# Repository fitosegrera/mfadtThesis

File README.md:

# mfadtThesis

####Setup UDOO Board

Install the VNC server:

1.Open a terminal window and type:

	sudo apt-get update

	sudo apt-get install tightvncserver

2. Run the server:

	vncserver :1 -geometry 800x600 -depth 24

3. Make the server run on every boot:

	sudo nano /etc/rc.local

The document will open on your terminal window, using your keyboard keys go to the line just before "exit0" and type:

	vncserver :1 -geometry 800x600 -depth 24 &

4. Before any further step, we will configure the udoo to have a STATIC IP Address. This in order to ensure the wireless connection to the local network. For the local network I'm using a linksis wireless router with a hidden network. To configure the udoo IP do the following:

	4.1 Go to Menu>Preferences>Network Connections

	4.2 Select the Wireless tab
	
	4.3 with your network name highlighted, click on EDIT

	4.4 go to the IPV4 tab and change from automatic to manual

	4.5 Finally Add a new IP Address(What ever address you want to assign to the udoo), a NETMASK (usually 255.255.255.0) and your GATEWAY(router's IP)

	4.6 Save your changes...

To remotly control your UDOO board you will need to install a VNC client. For windows and Mac I recomend REALVNC.
For linux xvncviewer. To install in linux go to your terminal and type:

	sudo apt-get install xvnc4viewer

To use the client from a linux computer type:

	sudo xvncviewer

Then just type your UDOO's ip followed by the port (replace udoo.ip.address with your udoo's ip address, the port remains the same):

	udoo.ip.address:5901

####Run a python script using foreverjs

	forever start -c python python_script.py

Stopping forever

	forever stopall

####htop process monitoring

	sudo apt-get install htop

to run the application type:

	htop

To filter processes to match only python scripts. Press the f4 key and in the text bar type: .py 

####PyPy

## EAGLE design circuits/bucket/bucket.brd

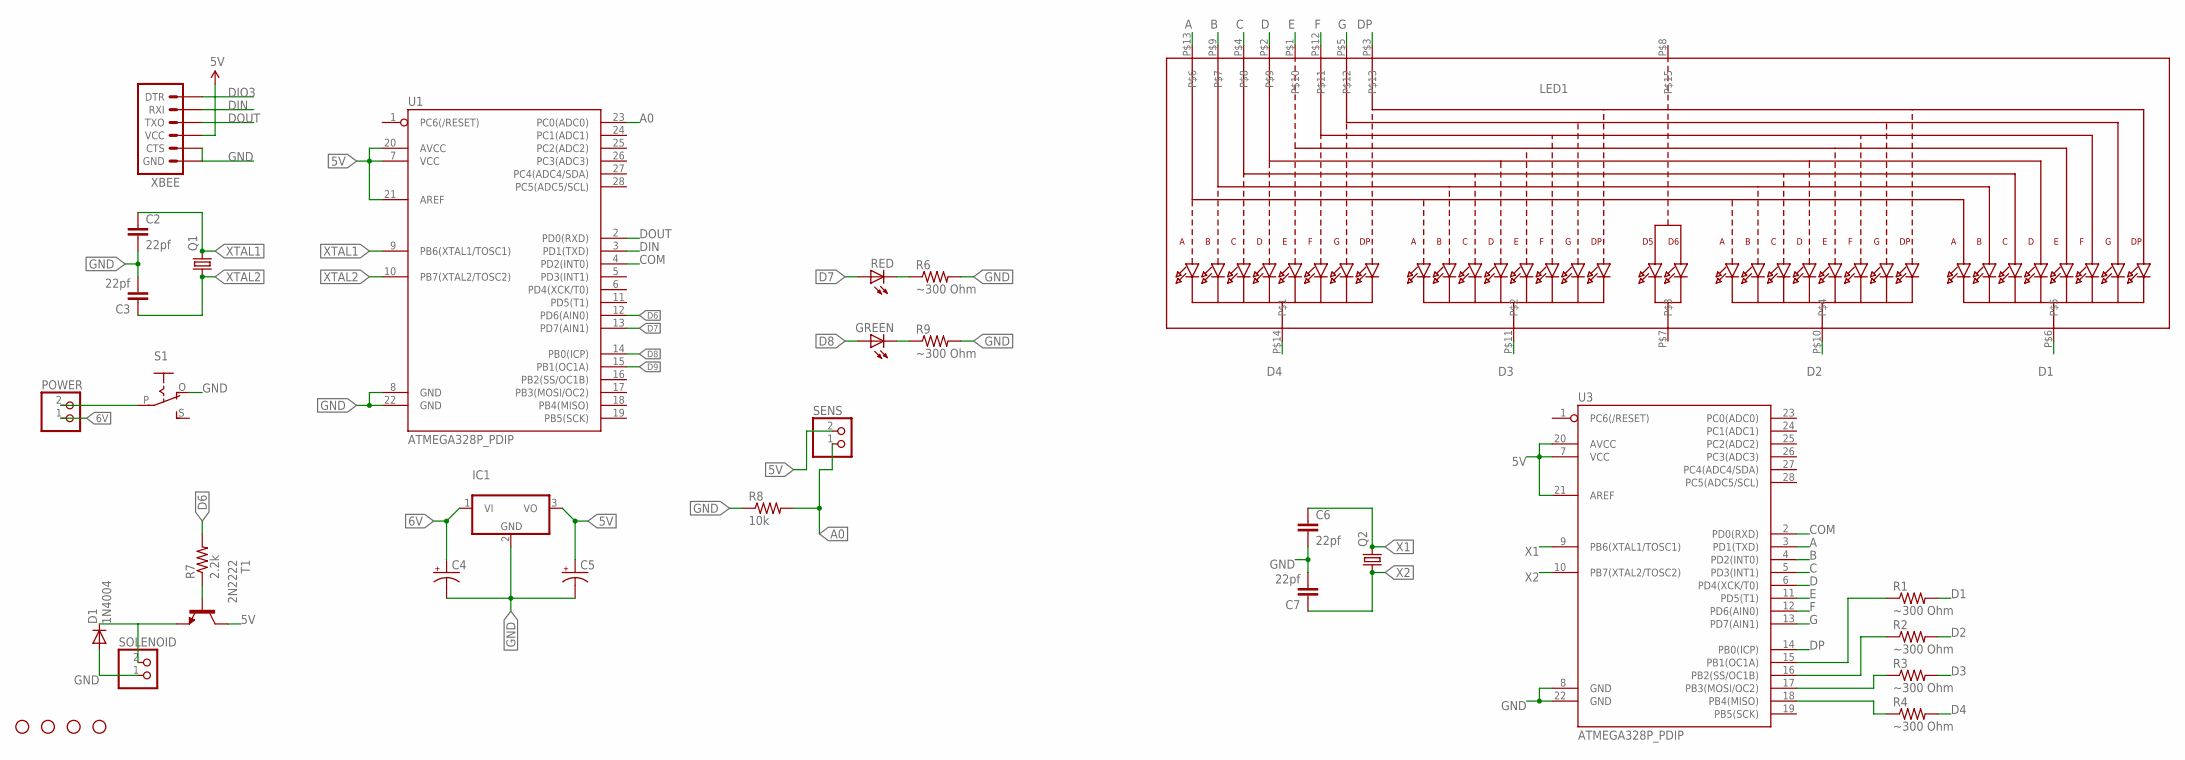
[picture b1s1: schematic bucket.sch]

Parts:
C2, C3, C6, C7: 22pf; 1206
C4, C5: CAP_POL1206; EIA3216
D1: 1N4004; DO41-10
GREEN: HSMC-C265
IC1: 7805T; TO220H
LED1: DISP_SEGMENT_4DIGIT_BL-Q56C43; SEGMENT-BL-Q56C43
POWER: JST_2PIN-THM-RA; JST-PH-2-THM-RA
Q1, Q2: CRYSTALHC49S; HC49/S
R1, R2, R3, R4, R6, R9: ~300 Ohm; 1206
R7: 2.2k; 1206
R8: 10k; 1206
RED: HSMC-C265
S1: EG1218S; EG1218
SENS: JST_2PIN-THM-RA; JST-PH-2-THM-RA
SOLENOID: JST_2PIN-THM-RA; JST-PH-2-THM-RA
STANDOFF1, STANDOFF2, STANDOFF3, STANDOFF4: STAND-OFF
T1: 2N2222; TO92-EBC-OVAL
U1, U3: ATMEGA328P_PDIP; DIL28-3
XBEE: ARDUINO_SERIAL_PROGRAMPTH; 1X06

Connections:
1: R1.1, U3.15 (PB1(OC1A))
2: R2.1, U3.16 (PB2(SS/OC1B))
3: R3.1, U3.17 (PB3(MOSI/OC2))
4: R4.1, U3.18 (PB4(MISO))
5V: C5.A (+), IC1.3 (VO), SENS.2 (1), T1.E (C), U1.7 (VCC), U1.20 (AVCC), U1.21 (AREF), U3.7 (VCC), U3.20 (AVCC), U3.21 (AREF), XBEE.4 (VCC)
6V: C4.A (+), IC1.1 (VI), POWER.1 (2)
A: LED1.P$13, U3.3 (PD1(TXD))
A0: R8.2, SENS.1 (2), U1.23 (PC0(ADC0))
B: LED1.P$9, U3.4 (PD2(INT0))
C: LED1.P$4, U3.5 (PD3(INT1))
COM: U1.4 (PD2(INT0)), U3.2 (PD0(RXD))
D: LED1.P$2, U3.6 (PD4(XCK/T0))
D1: LED1.P$6, R1.2
D2: LED1.P$10, R2.2
D3: LED1.P$11, R3.2
D4: LED1.P$14, R4.2
D6: R7.2, U1.12 (PD6(AIN0))
D7: RED.A, U1.13 (PD7(AIN1))
D8: GREEN.A, U1.14 (PB0(ICP))
D9: U1.15 (PB1(OC1A))
DIN: U1.3 (PD1(TXD)), XBEE.2 (RXI)
DIO3: XBEE.1 (DTR)
DOUT: U1.2 (PD0(RXD)), XBEE.3 (TXO)
DP: LED1.P$3, U3.14 (PB0(ICP))
E: LED1.P$1, U3.11 (PD5(T1))
F: LED1.P$12, U3.12 (PD6(AIN0))
G: LED1.P$5, U3.13 (PD7(AIN1))
GND: C2.2, C3.2, C4.C (-), C5.C (-), C6.2, C7.2, D1.A, IC1.2 (GND), R6.2, R8.1, R9.2, S1.O, SOLENOID.1 (2), U1.8 (GND), U1.22 (GND), U3.8 (GND), U3.22 (GND), XBEE.5 (CTS), XBEE.6 (GND)
unnamed: POWER.2 (1), S1.P
unnamed: D1.C, SOLENOID.2 (1), T1.C (E)
unnamed: R6.1, RED.C
unnamed: R7.1, T1.B
unnamed: GREEN.C, R9.1
X1: C6.1, Q2.2, U3.9 (PB6(XTAL1/TOSC1))
X2: C7.1, Q2.1, U3.10 (PB7(XTAL2/TOSC2))
XTAL1: C2.1, Q1.2, U1.9 (PB6(XTAL1/TOSC1))
XTAL2: C3.1, Q1.1, U1.10 (PB7(XTAL2/TOSC2))

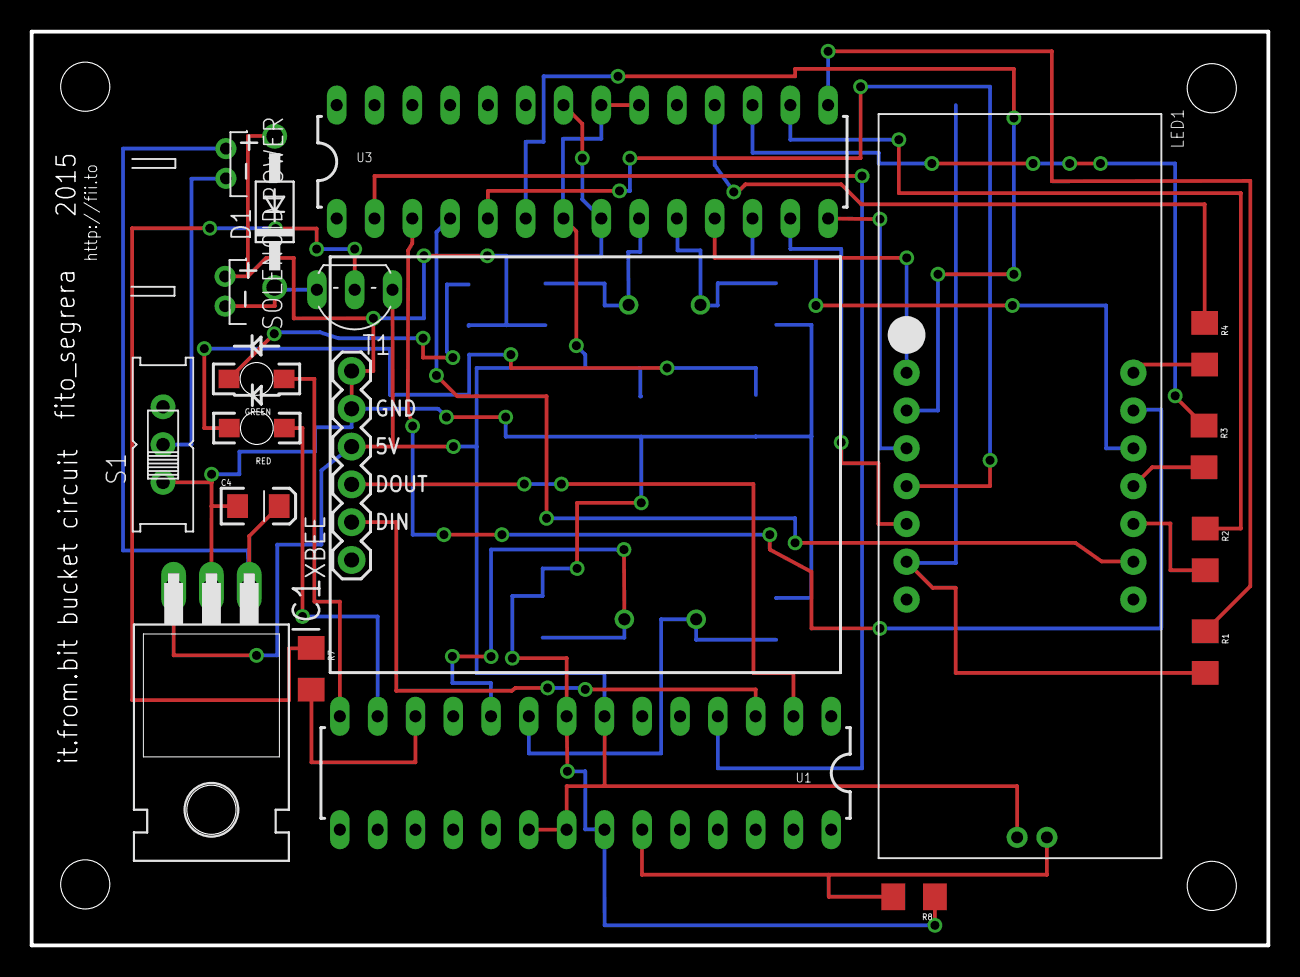
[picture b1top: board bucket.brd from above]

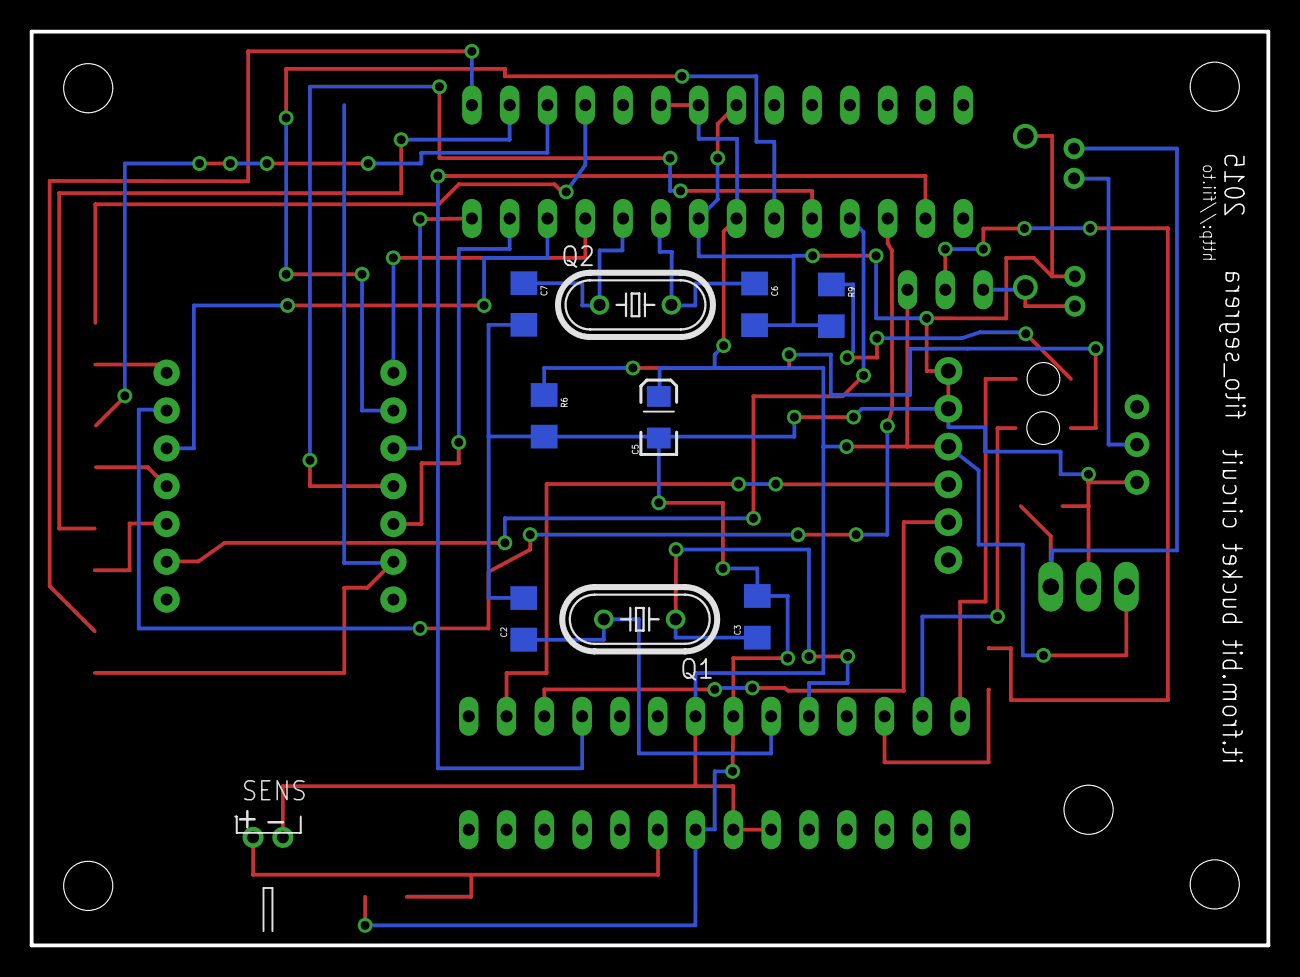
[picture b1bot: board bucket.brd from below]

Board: 2 copper layers, 83.1 x 61.4 mm, 33 parts (10 on the bottom side), 35 nets.

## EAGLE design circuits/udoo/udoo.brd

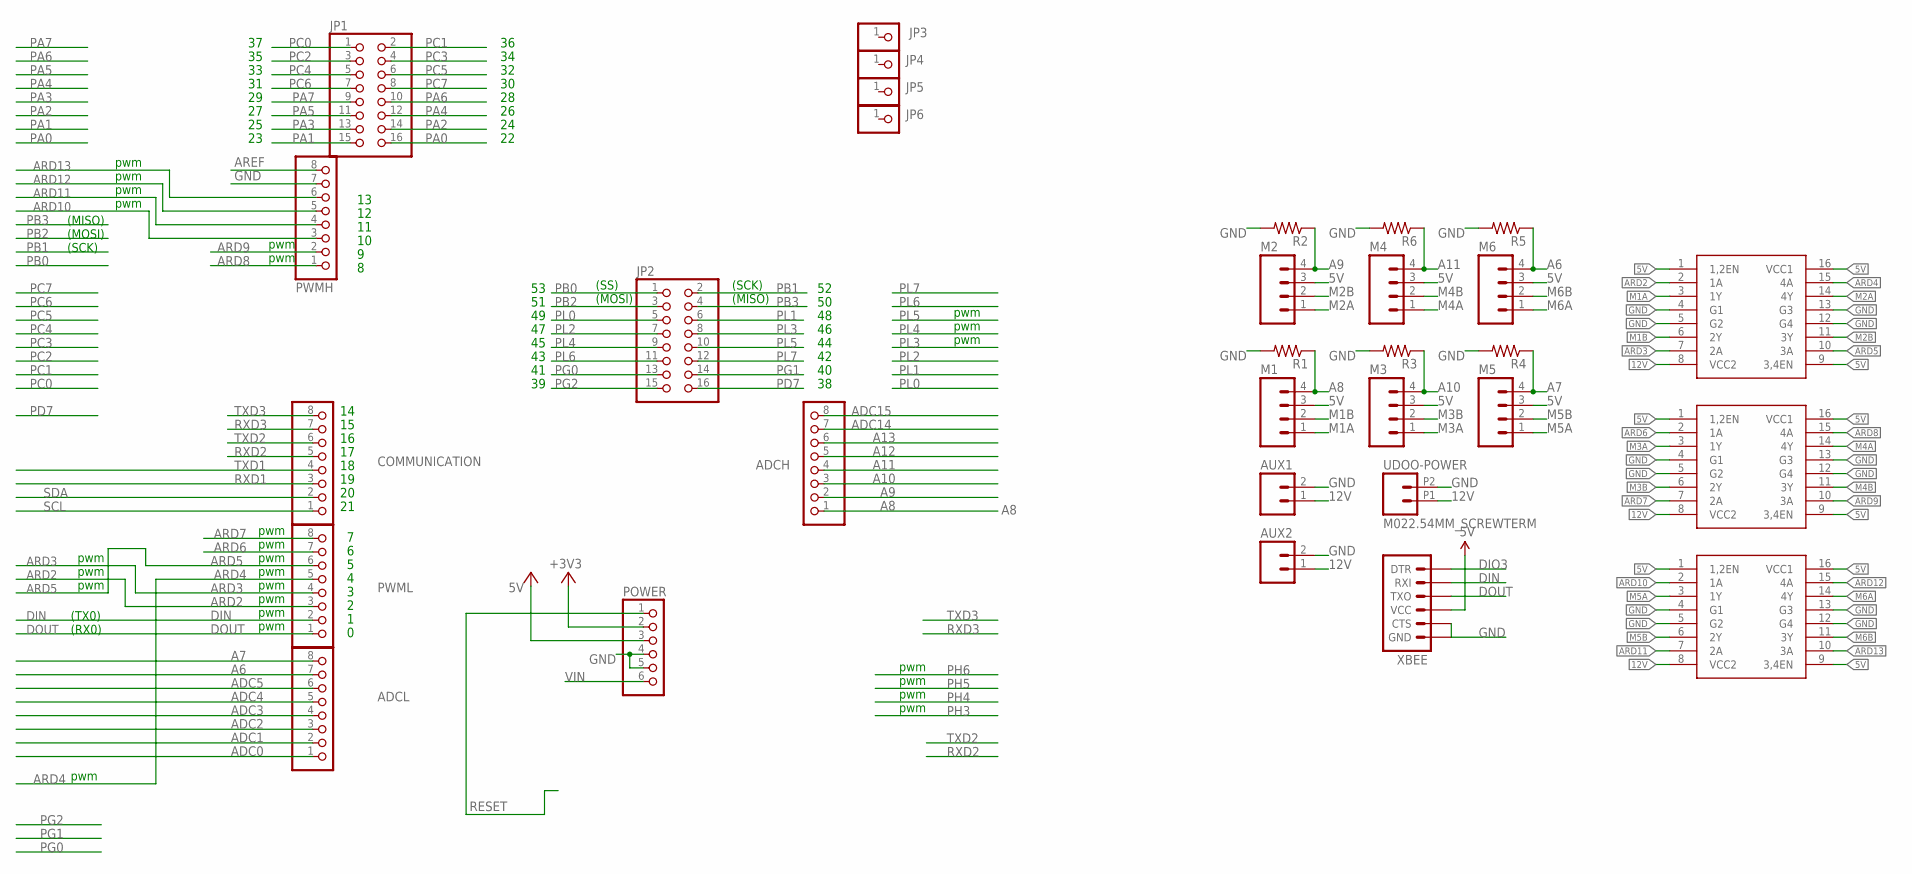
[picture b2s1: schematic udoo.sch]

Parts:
ADCH: PINHD-1X8; 1X08
ADCL: PINHD-1X8; 1X08
AUX1, AUX2: M02PTH; 1X02
COMMUNICATION: PINHD-1X8; 1X08
JP1, JP2: PINHD-2X8; 2X08
JP3, JP4, JP5, JP6: PINHD-1X1; 1X01
M1, M2, M3, M4, M5, M6: M04JST; 1X04-1.5MM_JST
POWER: PINHD-1X6; 1X06
PWMH: PINHD-1X8; 1X08
PWML: PINHD-1X8; 1X08
R1, R2, R3, R4, R5, R6: RESISTOR0805-RES; 0805
U$1, U$2, U$3: HBRIDGE
UDOO-POWER: M022.54MM_SCREWTERM; 1X02_2.54_SCREWTERM
XBEE: ARDUINO_SERIAL_PROGRAMPTH; 1X06

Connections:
5V: M1.3, M2.3, M3.3, M4.3, M5.3, M6.3, POWER.3, U$1.1 (1,2EN), U$1.9 (3,4EN), U$1.16 (VCC1), U$2.1 (1,2EN), U$2.9 (3,4EN), U$2.16 (VCC1), U$3.1 (1,2EN), U$3.9 (3,4EN), U$3.16 (VCC1), XBEE.4 (VCC)
12V: AUX1.1, AUX2.1, U$1.8 (VCC2), U$2.8 (VCC2), U$3.8 (VCC2), UDOO-POWER.P1 (1)
+3V3: POWER.2
A6: ADCL.7, M6.4, R5.1
A7: ADCL.8, M5.4, R4.1
A8: ADCH.1, M1.4, R1.1
A9: ADCH.2, M2.4, R2.1
A10: ADCH.3, M3.4, R3.1
A11: ADCH.4, M4.4, R6.1
A12: ADCH.5
A13: ADCH.6
ADC0: ADCL.1
ADC1: ADCL.2
ADC2: ADCL.3
ADC3: ADCL.4
ADC4: ADCL.5
ADC5: ADCL.6
ADC14: ADCH.7
ADC15: ADCH.8
ARD2: PWML.3, U$1.2 (1A)
ARD3: PWML.4, U$1.7 (2A)
ARD4: PWML.5, U$1.15 (4A)
ARD5: PWML.6, U$1.10 (3A)
ARD6: PWML.7, U$2.2 (1A)
ARD7: PWML.8, U$2.7 (2A)
ARD8: PWMH.1, U$2.15 (4A)
ARD9: PWMH.2, U$2.10 (3A)
ARD10: PWMH.3, U$3.2 (1A)
ARD11: PWMH.4, U$3.7 (2A)
ARD12: PWMH.5, U$3.15 (4A)
ARD13: PWMH.6, U$3.10 (3A)
AREF: PWMH.8
DIN: PWML.2, XBEE.2 (RXI)
DIO3: XBEE.1 (DTR)
DOUT: PWML.1, XBEE.3 (TXO)
GND: AUX1.2, AUX2.2, POWER.4, POWER.5, PWMH.7, R1.2, R2.2, R3.2, R4.2, R5.2, R6.2, U$1.4 (G1), U$1.5 (G2), U$1.12 (G4), U$1.13 (G3), U$2.4 (G1), U$2.5 (G2), U$2.12 (G4), U$2.13 (G3), U$3.4 (G1), U$3.5 (G2), U$3.12 (G4), U$3.13 (G3), UDOO-POWER.P2 (2), XBEE.5 (CTS), XBEE.6 (GND)
M1A: M1.1, U$1.3 (1Y)
M1B: M1.2, U$1.6 (2Y)
M2A: M2.1, U$1.14 (4Y)
M2B: M2.2, U$1.11 (3Y)
M3A: M3.1, U$2.3 (1Y)
M3B: M3.2, U$2.6 (2Y)
M4A: M4.1, U$2.14 (4Y)
M4B: M4.2, U$2.11 (3Y)
M5A: M5.1, U$3.3 (1Y)
M5B: M5.2, U$3.6 (2Y)
M6A: M6.1, U$3.14 (4Y)
M6B: M6.2, U$3.11 (3Y)
PA0: JP1.16
PA1: JP1.15
PA2: JP1.14
PA3: JP1.13
PA4: JP1.12
PA5: JP1.11
PA6: JP1.10
PA7: JP1.9
PB0: JP2.1
PB1: JP2.2
PB2: JP2.3
PB3: JP2.4
PC0: JP1.1
PC1: JP1.2
PC2: JP1.3
PC3: JP1.4
PC4: JP1.5
PC5: JP1.6
PC6: JP1.7
PC7: JP1.8
PD7: JP2.16
PG0: JP2.13
PG1: JP2.14
PG2: JP2.15
PL0: JP2.5
PL1: JP2.6
PL2: JP2.7
PL3: JP2.8
PL4: JP2.9
PL5: JP2.10
PL6: JP2.11
PL7: JP2.12
RESET: POWER.1
RXD1: COMMUNICATION.3
RXD2: COMMUNICATION.5
RXD3: COMMUNICATION.7
SCL: COMMUNICATION.1
SDA: COMMUNICATION.2
TXD1: COMMUNICATION.4
TXD2: COMMUNICATION.6
TXD3: COMMUNICATION.8
VIN: POWER.6

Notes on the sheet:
pwm
(TX0)
(RX0)
(MISO)
(SCK)
(MOSI)
(SS)

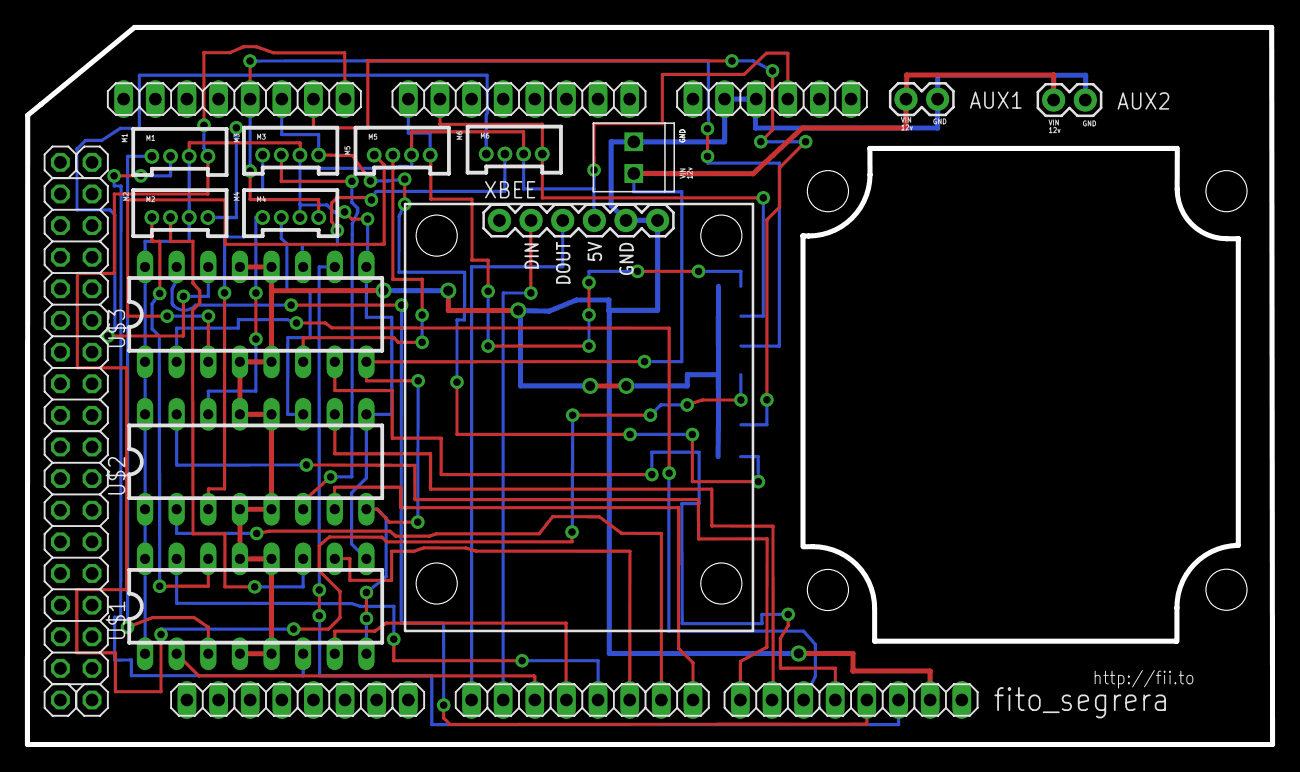
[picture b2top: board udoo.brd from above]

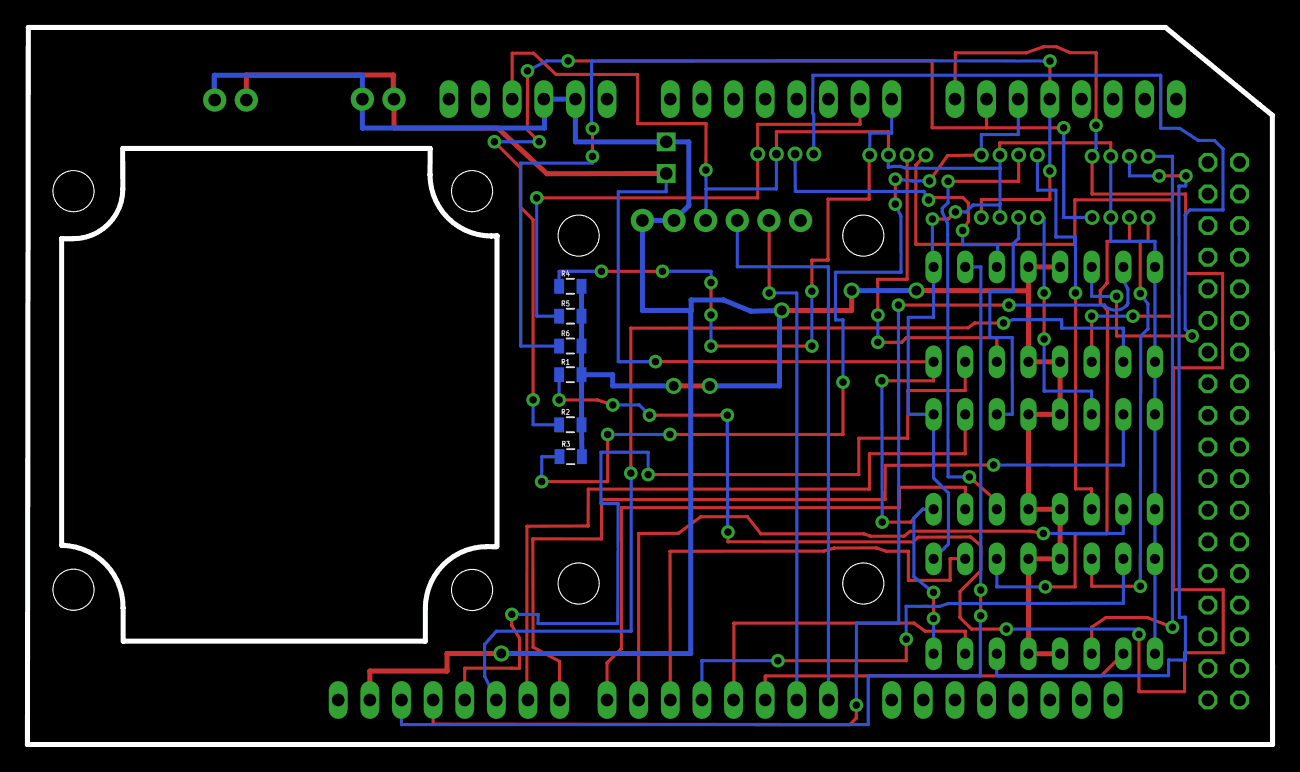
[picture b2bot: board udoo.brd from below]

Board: 2 copper layers, 100.0 x 57.6 mm, 39 parts (6 on the bottom side), 35 nets.

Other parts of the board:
U$4, U$5, U$6, U$7, U$8, U$9, U$10, U$11: STAND-OFF

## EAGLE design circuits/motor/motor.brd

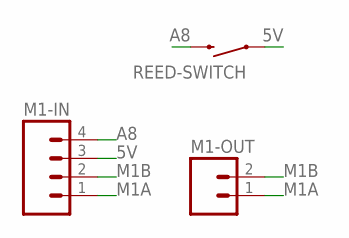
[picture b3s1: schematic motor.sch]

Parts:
M1-IN: M04JST; 1X04-1.5MM_JST
M1-OUT: M02JST-PTH-2; JST-2-PTH
REED-SWITCH: SWITCH-MOMENTARY-2PTH_REED2; REED_SWITCH_PLASTIC

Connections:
5V: M1-IN.3, REED-SWITCH.P$1 (1)
A8: M1-IN.4, REED-SWITCH.P$2 (2)
M1A: M1-IN.1, M1-OUT.1
M1B: M1-IN.2, M1-OUT.2

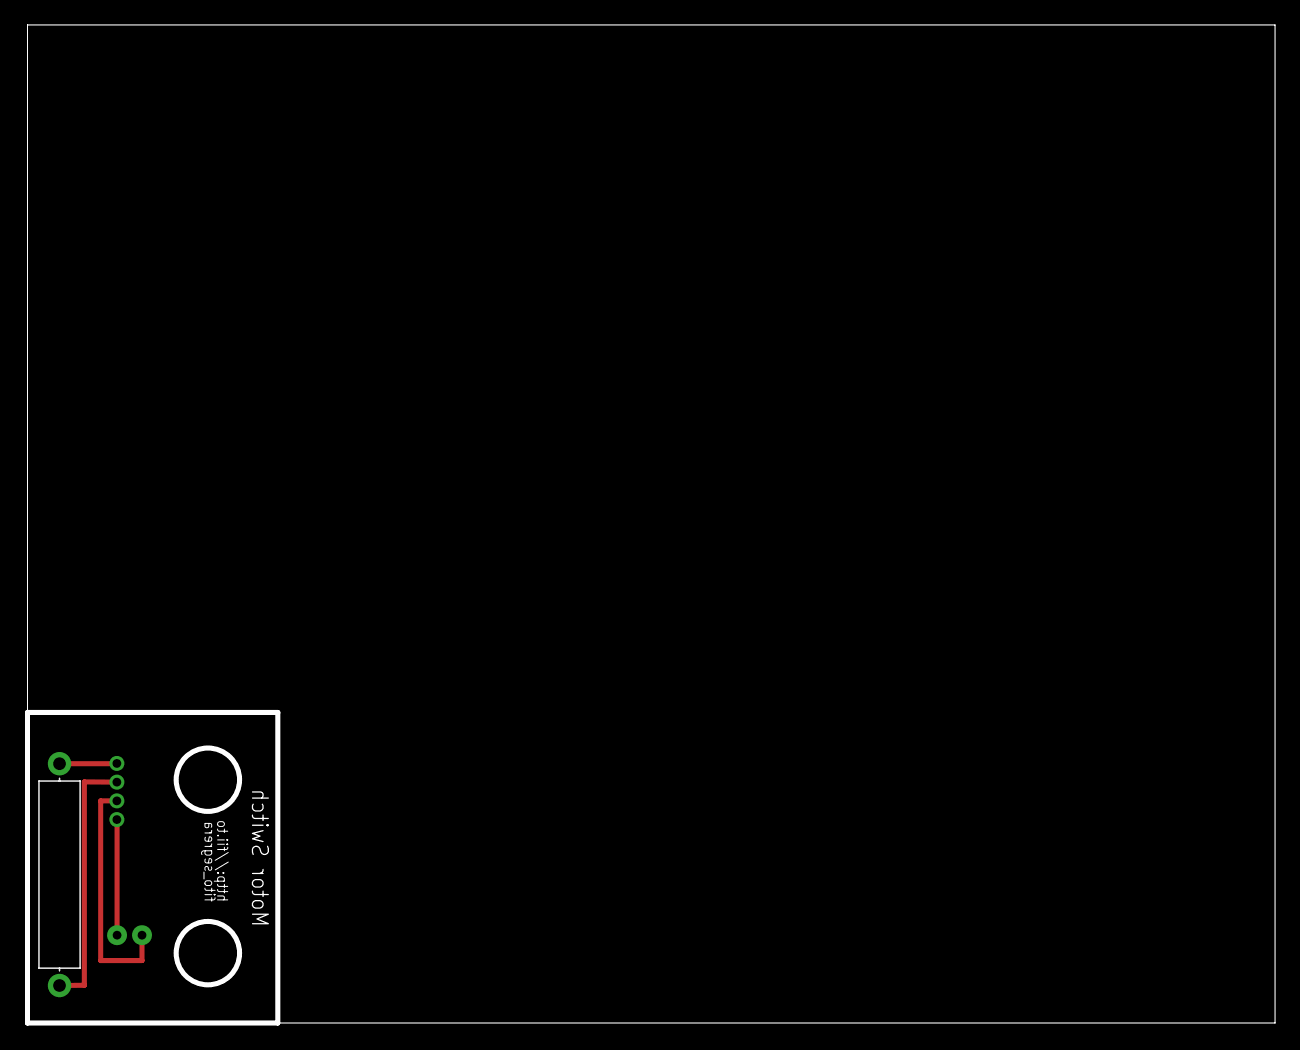
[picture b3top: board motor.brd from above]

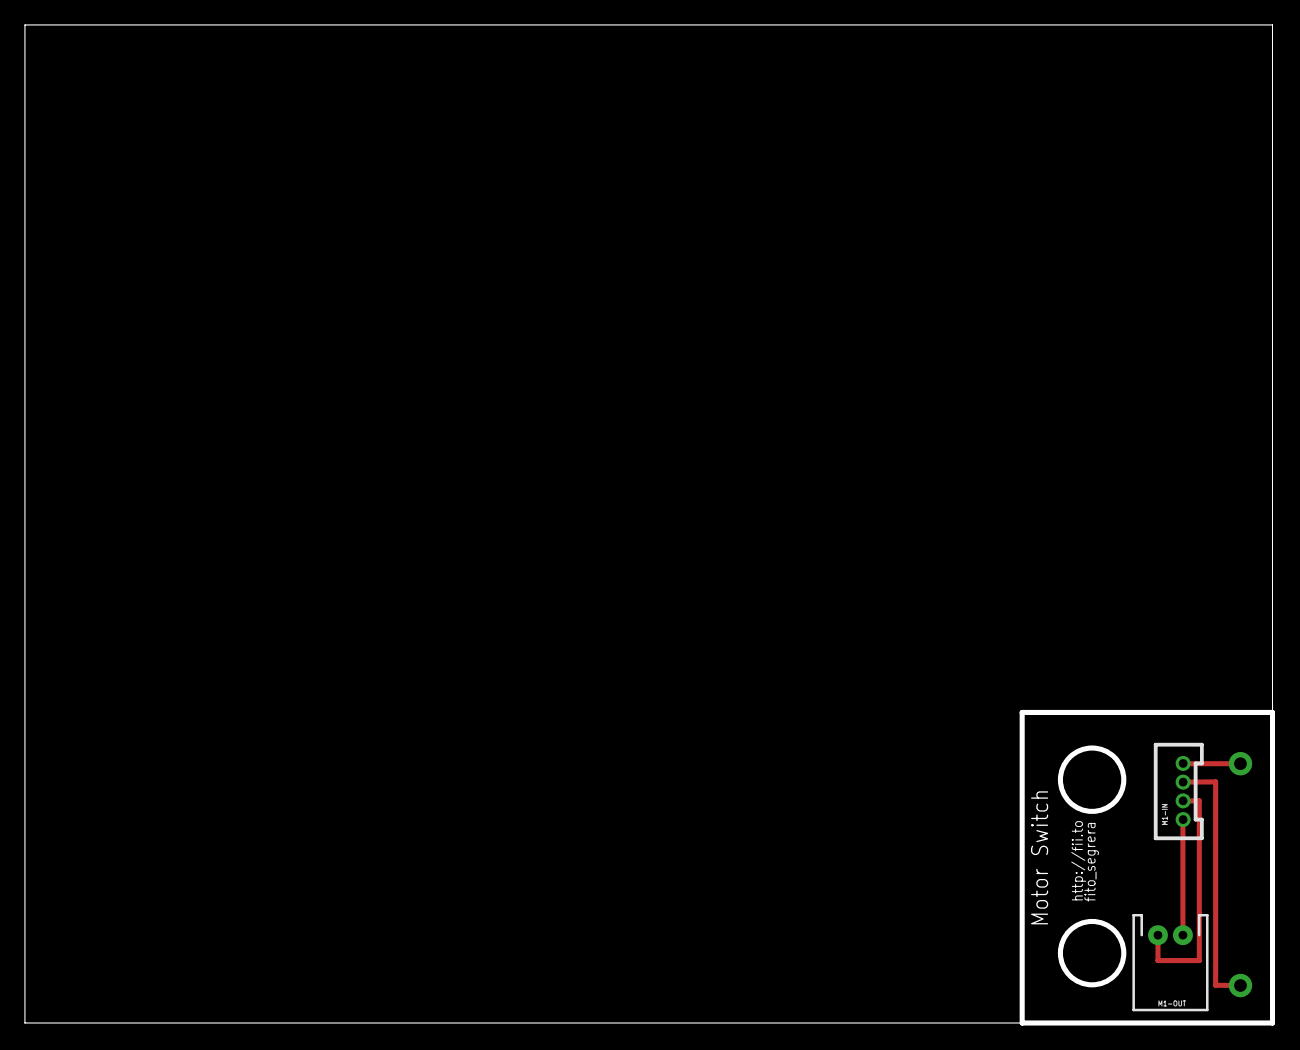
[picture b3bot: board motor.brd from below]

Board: 2 copper layers, 100.0 x 80.0 mm, 3 parts (2 on the bottom side), 4 nets.

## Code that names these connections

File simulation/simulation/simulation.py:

#!/usr/bin python

from simlib import emitter, bucket, udooGPIO

hit = 0
udoo = udooGPIO.UdooGPIO()

#Declare GPIOs
m1a = 16
m1b = 20
m2a = 17
m2b = 18
m3a = 41
m3b = 42
m4a = 21
m4b = 19
m5a = 1
m5b = 9

def setup():
	udoo.Serial(9600)
	udoo.pinMode(3, "OUTPUT")
	udoo.digitalWrite(3, "LOW")
	udoo.pinMode(m1a, "OUTPUT")
	udoo.pinMode(m1b, "OUTPUT")
	udoo.digitalWrite(m1a, "LOW")
	udoo.digitalWrite(m1b, "LOW")

def runMotor(a, b, direction, delay):
	if direction == "down":
		udoo.digitalWrite(a, "HIGH")
		udoo.digitalWrite(b, "LOW")
	elif direction == "up":
		udoo.digitalWrite(a, "LOW")
		udoo.digitalWrite(b, "HIGH")
	udoo.delay(delay)
		
def stopMotor(a, b):
	udoo.digitalWrite(a, "LOW")
	udoo.digitalWrite(b, "LOW")
	
# Simulation function
def startSim():
	global hit, s
	n = 5
	e = [None]*n
	b = [None]*n
	buckInitPos = 0
	simCount = 0
	for i in range(n):
		e[i] = emitter.Emitter(0)
		b[i] = bucket.Bucket(buckInitPos)

	while True:
		for i in range(n):
			collided = e[i].generateSystem()
			if collided == True:
				b[i].update()
				print "bitDrop HIT bucket#", i+1
				hit = i+1
				if hit == 1:
					udoo.SerialWrite('1;%')
					udoo.delay(0.1)
					udoo.digitalWrite(3, "HIGH")
					runMotor(m1a, m1b, "down", 0.01)
				elif hit == 2:
					udoo.SerialWrite('2;%')
					udoo.delay(0.1)
					udoo.digitalWrite(3, "HIGH")
					runMotor(m2a, m2b, "down", 0.01)
				elif hit == 3:
					udoo.SerialWrite('3;%')
					udoo.delay(0.1)
					udoo.digitalWrite(3, "HIGH")
					runMotor(m3a, m3b, "down", 0.01)
				elif hit == 4:
					udoo.SerialWrite('4;%')
					udoo.delay(0.1)
					udoo.digitalWrite(3, "HIGH")
					runMotor(m4a, m4b, "down", 0.01)
				elif hit == 5:
					udoo.SerialWrite('5;%')
					udoo.delay(0.1)
					udoo.digitalWrite(3, "HIGH")
					runMotor(m5a, m5b, "down", 0.01)

			udoo.SerialWrite('0;%')
			udoo.digitalWrite(3, "LOW")
			stopMotor(m1a, m1b)

if __name__ == "__main__":
	setup()
	startSim()

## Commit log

2015-04-25 pins correction

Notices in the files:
parts and their libraries:
SparkFun-DigitalIC: Licensing: Creative Commons ShareAlike 4.0 International - https://creativecommons.org/licenses/by-sa/4.0
